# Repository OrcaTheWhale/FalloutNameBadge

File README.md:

# FalloutNameBadge

Slack: OrcaTheWhale

I am late to the deadline, and folders aren't uploading(for some reason), so that's why the repo is a little mess right now.

This name badge is an over-engineered badge to light up and provide a unique NFC tag depending on the tilt.

Utilizing an RP2040 and essentially being a clone board without breaking GPIOs, the FalloutNameBadge utilizes an accelerometer to detect tilt, and based on the tilt, lights up one of four LED's, and one of four links.

IMPORTANT INFORMATION FOR STAFF.
- IDK WHY MY PCBS DO THIS; THE PCB IS 2 LAYERS ONLY, AND SWITCH VIAS TO TENTED.

GO PCB BARE ONLY!!! HOW IS IT POSSIBLE TO RUN OUT OF RP2040S JLCPCB???

Front:

Back:

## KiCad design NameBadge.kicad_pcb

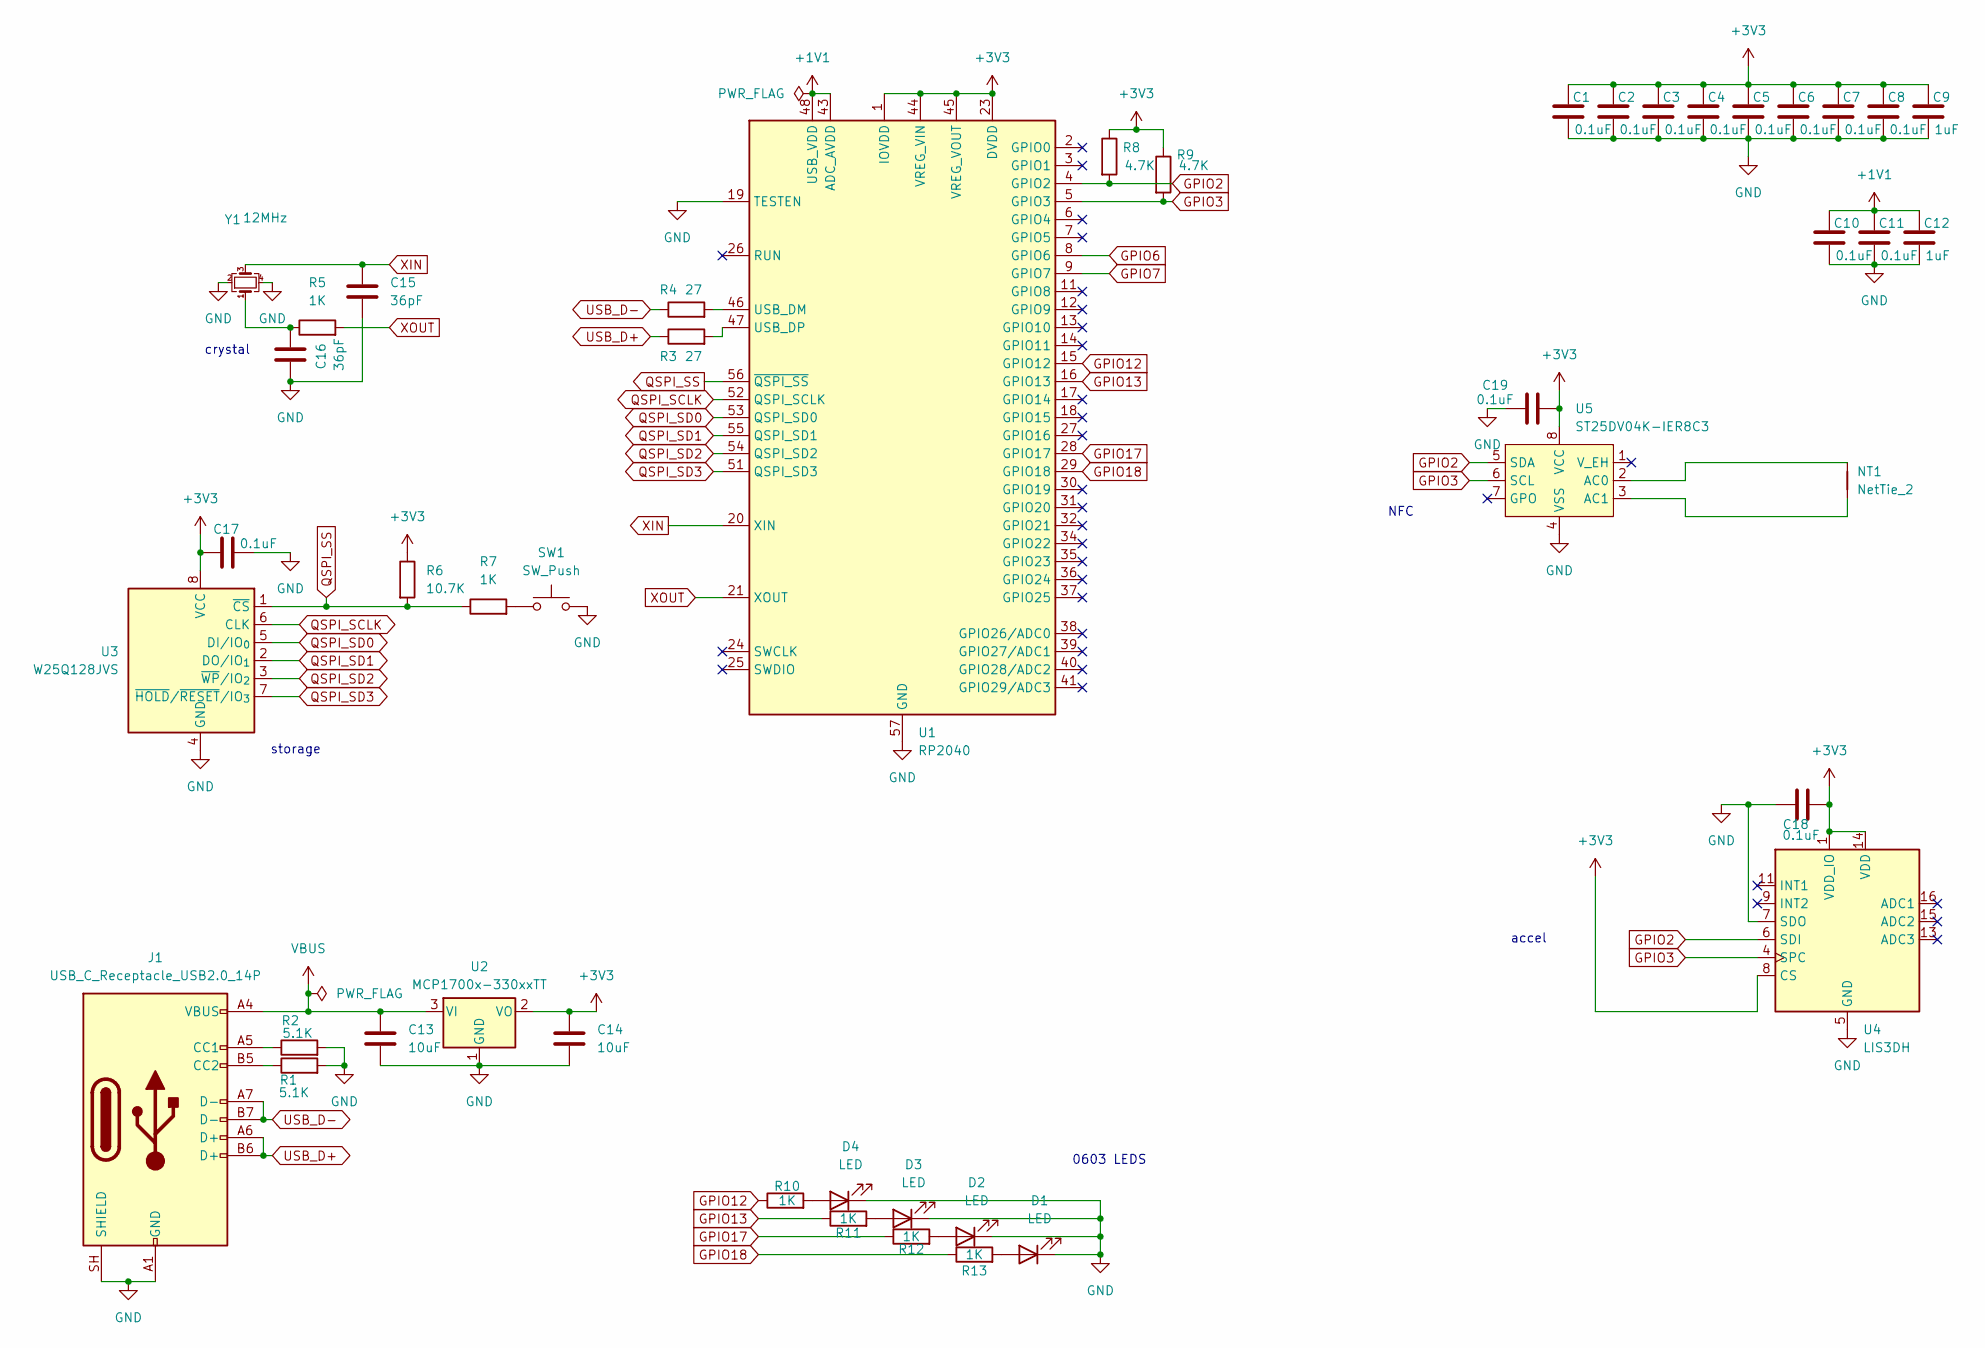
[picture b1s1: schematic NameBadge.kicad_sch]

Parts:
C1, C2, C3, C4, C5, C6, C7, C8, C10, C11: 0.1uF; C_0402_1005Metric_Pad0.74x0.62mm_HandSolder
C9, C12: 1uF; C_0402_1005Metric_Pad0.74x0.62mm_HandSolder
C13, C14: 10uF; C_0603_1608Metric
C15, C16: 36pF; C_0402_1005Metric
C17, C18, C19: 0.1uF; C_0402_1005Metric
D1, D2, D3, D4: LED; LED_0402_1005Metric
J1: USB_C_Receptacle_USB2.0_14P; USB_C_Receptacle_HRO_TYPE-C-31-M-12
NT1: NetTie_2; NetTie-2_SMD_Pad0.5mm
R1, R2: 5.1K; R_0402_1005Metric
R3, R4: 27; R_0402_1005Metric
R5, R7, R10, R11, R12, R13: 1K; R_0402_1005Metric
R6: 10.7K; R_0402_1005Metric
R8, R9: 4.7K; R_0402_1005Metric
SW1: SW_Push; SW_PUSH_6mm
U1: RP2040; QFN-56-1EP_7x7mm_P0.4mm_EP3.2x3.2mm
U2: MCP1700x-330xxTT; SOT-23
U3: W25Q128JVS; Winbond_USON-8-1EP_3x2mm_P0.5mm_EP0.2x1.6mm
U4: LIS3DH; LGA-16_3x3mm_P0.5mm_LayoutBorder3x5y
U5: ST25DV04K-IER8C3; DFN-8-1EP_3x2mm_P0.5mm_EP1.36x1.46mm
Y1: 12MHz; Crystal_SMD_3225-4Pin_3.2x2.5mm

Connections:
+1V1: C10.1, C11.1, C12.1, U1.43 (ADC_AVDD), U1.48 (USB_VDD)
+3V3: C1.1, C2.1, C3.1, C4.1, C5.1, C6.1, C7.1, C8.1, C9.1, C14.1, C17.1, C18.2, C19.2, R6.1, R8.1, R9.1, U1.1 (IOVDD), U1.10 (IOVDD), U1.22 (IOVDD), U1.23 (DVDD), U1.33 (IOVDD), U1.42 (IOVDD), U1.44 (VREG_VIN), U1.45 (VREG_VOUT), U1.49 (IOVDD), U1.50 (DVDD), U2.2 (VO), U3.8 (VCC), U4.1 (VDD_IO), U4.8 (CS), U4.14 (VDD), U5.8 (VCC)
GND: C1.2, C2.2, C3.2, C4.2, C5.2, C6.2, C7.2, C8.2, C9.2, C10.2, C11.2, C12.2, C13.2, C14.2, C15.1, C16.1, C17.2, C18.1, C19.1, D1.1 (K), D2.1 (K), D3.1 (K), D4.1 (K), J1.A1 (GND), J1.A12 (GND), J1.B1 (GND), J1.B12 (GND), J1.SH (SHIELD), R1.2, R2.2, SW1.2, U1.19 (TESTEN), U1.57 (GND), U2.1 (GND), U3.4 (GND), U4.5 (GND), U4.7 (SDO), U4.10 (GND), U4.12 (GND), U5.4 (VSS), Y1.2 (G), Y1.4 (G)
GPIO2: R8.2, U1.4 (GPIO2), U4.6 (SDI), U5.5 (SDA)
GPIO3: R9.2, U1.5 (GPIO3), U4.4 (SPC), U5.6 (SCL)
GPIO6: U1.8 (GPIO6)
GPIO7: U1.9 (GPIO7)
GPIO12: R10.1, U1.15 (GPIO12)
GPIO13: R11.1, U1.16 (GPIO13)
GPIO17: R12.1, U1.28 (GPIO17)
GPIO18: R13.1, U1.29 (GPIO18)
unnamed: C16.2, R5.1, Y1.1
unnamed: D1.2 (A), R13.2
unnamed: D2.2 (A), R12.2
unnamed: D3.2 (A), R11.2
unnamed: D4.2 (A), R10.2
unnamed: J1.A5 (CC1), R2.1
unnamed: J1.B5 (CC2), R1.1
unnamed: NT1.2, U5.2 (AC0)
unnamed: NT1.1, U5.3 (AC1)
unnamed: R7.2, SW1.1
unnamed: R4.2, U1.46 (USB_DM)
unnamed: R3.2, U1.47 (USB_DP)
QSPI_SCLK: U1.52 (QSPI_SCLK), U3.6 (CLK)
QSPI_SD0: U1.53 (QSPI_SD0), U3.5 (DI/IO_{0})
QSPI_SD1: U1.55 (QSPI_SD1), U3.2 (DO/IO_{1})
QSPI_SD2: U1.54 (QSPI_SD2), U3.3 (~WP/IO_{2})
QSPI_SD3: U1.51 (QSPI_SD3), U3.7 (~HOLD/~RESET/IO_{3})
QSPI_SS: R6.2, R7.1, U1.56 (~QSPI_SS), U3.1 (~CS)
USB_D+: J1.A6 (D+), J1.B6 (D+), R3.1
USB_D-: J1.A7 (D-), J1.B7 (D-), R4.1
VBUS: C13.1, J1.A4 (VBUS), J1.A9 (VBUS), J1.B4 (VBUS), J1.B9 (VBUS), U2.3 (VI)
XIN: C15.2, U1.20 (XIN), Y1.3
XOUT: R5.2, U1.21 (XOUT)

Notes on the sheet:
storage
accel
crystal
0603 LEDS
NFC

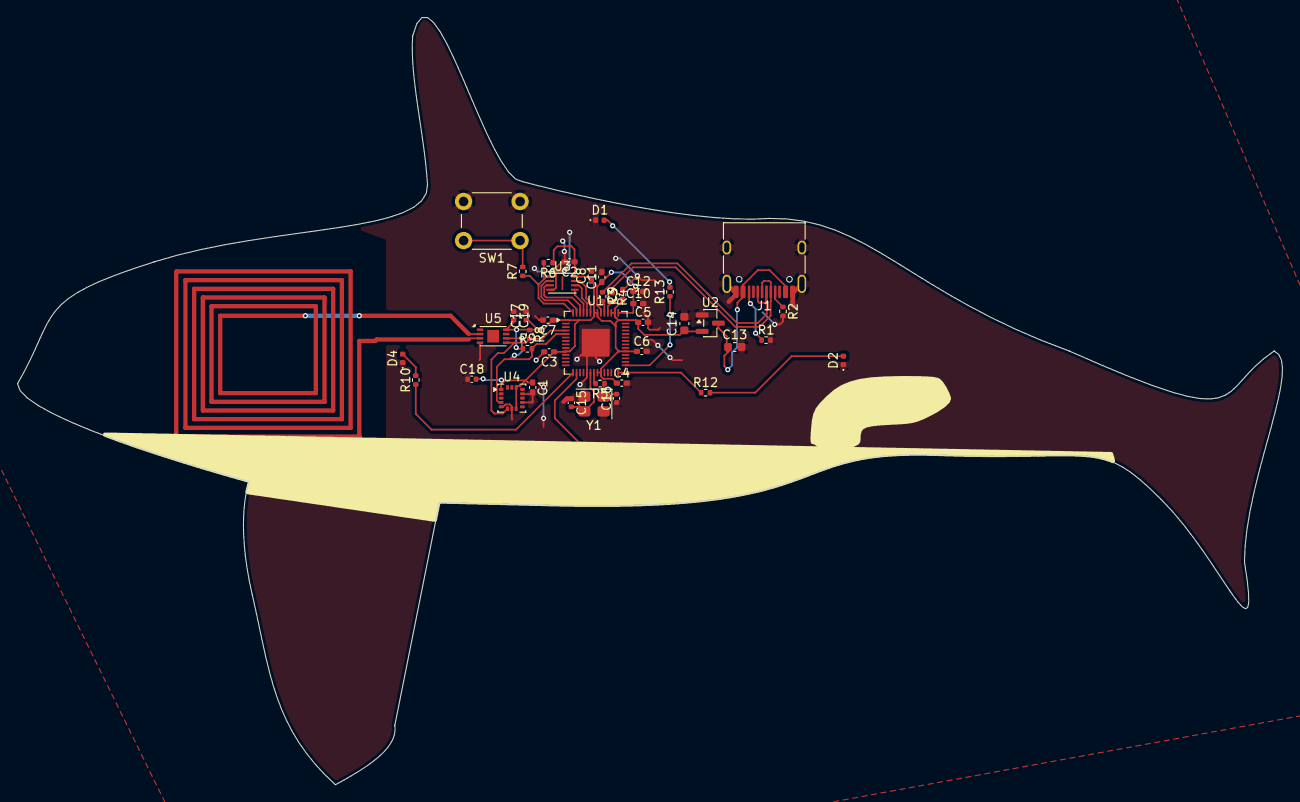
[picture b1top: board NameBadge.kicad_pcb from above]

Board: 4 copper layers, 145.5 x 88.3 mm, 45 parts (0 on the bottom side), 32 nets.

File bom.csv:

Designator,Footprint,Quantity,Value,LCSC Part #
"C1, C10, C11, C17, C18, C19, C2, C3, C4, C5, C6, C7, C8",0402,13,0.1uF,
"C12, C9",0402,2,1uF,
"C13, C14",0603,2,10uF,
"C15, C16",0402,2,36pF,
"D1, D2, D3, D4",0402,4,LED,
J1,USB_C_Receptacle_HRO_TYPE-C-31-M-12,1,USB_C_Receptacle_USB2.0_14P,
"R1, R2",0402,2,5.1K,
"R10, R11, R12, R13, R5, R7",0402,6,1K,
"R3, R4",0402,2,27,
R6,0402,1,10.7K,
"R8, R9",0402,2,4.7K,
SW1,SW_PUSH_6mm,1,SW_Push,
U1,QFN-56-1EP_7x7mm_P0.4mm_EP3.2x3.2mm,1,RP2040,
U2,SOT-23,1,MCP1700x-330xxTT,
U3,Winbond_USON-8-1EP_3x2mm_P0.5mm_EP0.2x1.6mm,1,W25Q128JVS,
U4,LGA-16_3x3mm_P0.5mm_LayoutBorder3x5y,1,LIS3DH,
U5,DFN-8-1EP_3x2mm_P0.5mm_EP1.36x1.46mm,1,ST25DV04K-IER8C3,
Y1,Crystal_SMD_3225-4Pin_3.2x2.5mm,1,12MHz,
